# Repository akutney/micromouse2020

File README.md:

# Getting Started

Get started with the following links:

- [Environment Setup](docs/Environment%20Setup.md)
- [Project Structure](docs/Project%20Structure.md)
- [Development Lifecycle](docs/Development%20Lifecycle.md)

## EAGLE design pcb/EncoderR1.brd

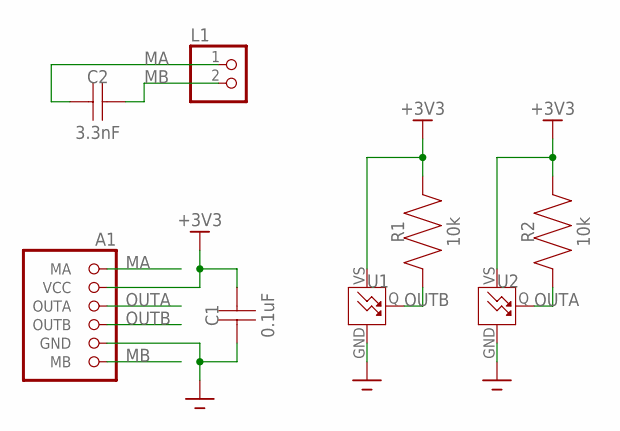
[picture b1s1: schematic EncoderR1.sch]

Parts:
A1: ENCODER; ENCODER-TAB
C1: 0.1uF; 0603
C2: 3.3nF; 0603
L1: MOTOR
R1, R2: 10k; 0603
U1, U2: TLE49462KHTSA1

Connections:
+3V3: A1.2 (VCC), C1.2, R1.2, R2.2, U1.VS, U2.VS
GND: A1.5 (GND), C1.1, U1.GND, U2.GND
MA: A1.1 (MA), C2.1, L1.1
MB: A1.6 (MB), C2.2, L1.2
OUTA: A1.3 (OUTA), R2.1, U2.Q
OUTB: A1.4 (OUTB), R1.1, U1.Q

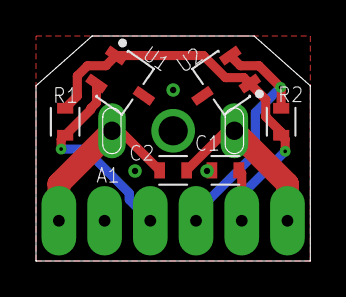
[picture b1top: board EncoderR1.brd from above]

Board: 2 copper layers, 15.2 x 12.5 mm, 8 parts (0 on the bottom side), 6 nets.

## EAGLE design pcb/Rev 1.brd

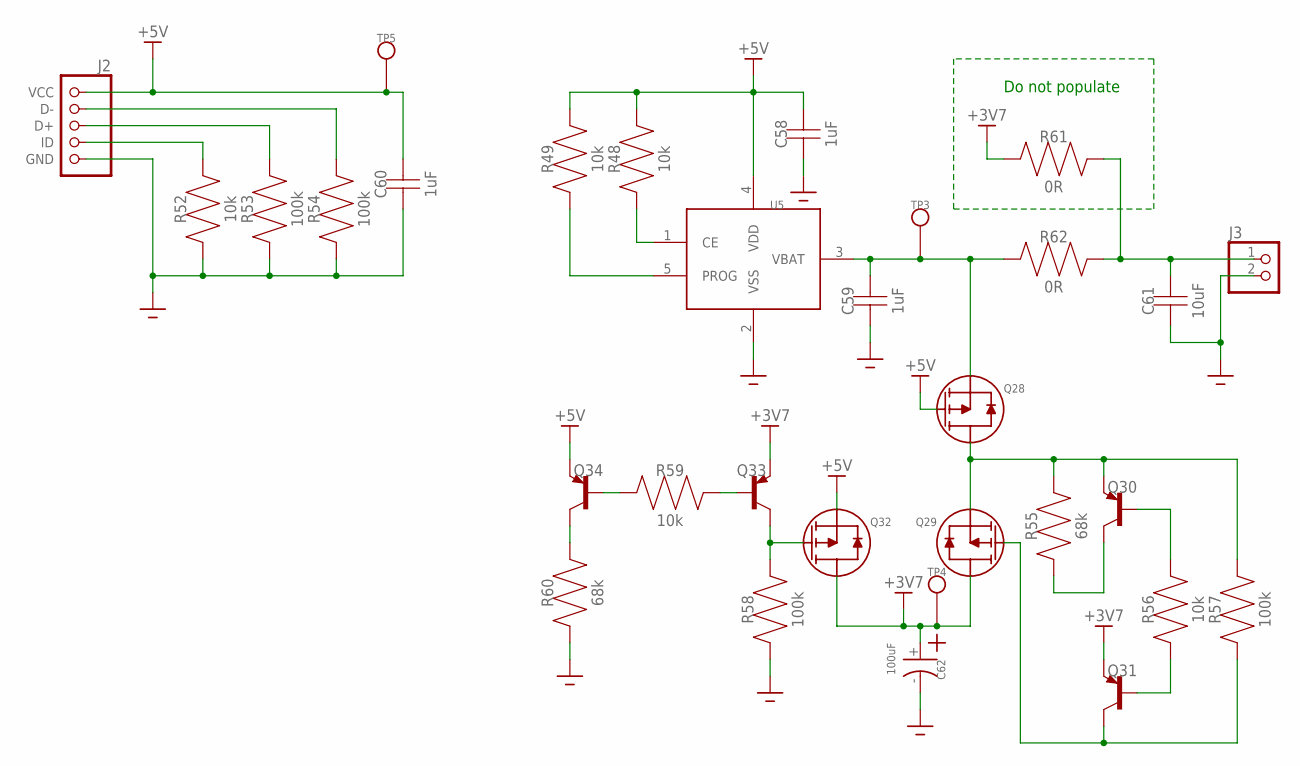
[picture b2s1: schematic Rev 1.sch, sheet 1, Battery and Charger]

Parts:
C58, C59, C60: 1uF; 0805
C61: 10uF; 0805
C62: 100uF; EEE-1EA101AP
J2: 10118194-0001LF
J3: B2B-PH-K-S(LF)(SN)
Q28, Q29, Q32: SI7157DP
Q30, Q31, Q33, Q34: MMBT3906; SOT96P237X112-3
R48, R49, R52: 10k; 0402
R53, R54: 100k; 0402
R55: 68k; 0603
R56: 10k; 0603
R57: 100k; 0603
R58: 100k; 0805
R59: 10k; 0805
R60: 68k; 0805
R61, R62: 0R; 0805
TP3, TP4, TP5: TESTPOINT
U5: MCP73811

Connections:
+3V7: C62.+, Q29.5 (D), Q29.6 (D), Q29.7 (D), Q29.8 (D), Q29.9 (D), Q29.10 (D), Q29.11 (D), Q31.2 (E), Q32.5 (D), Q32.6 (D), Q32.7 (D), Q32.8 (D), Q32.9 (D), Q32.10 (D), Q32.11 (D), Q33.2 (E), R61.P$1, TP4.P1; also elsewhere on the board
+5V: C58.P$2, C60.P$2, J2.1 (VCC), Q28.4 (G), Q32.1 (S), Q32.2 (S), Q32.3 (S), Q34.2 (E), R48.2, R49.2, TP5.P1, U5.4 (VDD)
GND: C58.P$1, C59.P$1, C60.P$1, C61.P$1, C62.-, J2.5 (GND), J2.6 (GND), J2.7 (GND), J2.8 (GND), J2.9 (GND), J2.10 (GND), J2.11 (GND), J2.12 (GND), J2.13 (GND), J2.14 (GND), J2.15 (GND), J3.2, R52.1, R53.1, R54.1, R58.P$1, R60.P$1, U5.2 (VSS); also elsewhere on the board
unnamed: C59.P$2, Q28.1 (S), Q28.2 (S), Q28.3 (S), R62.P$1, TP3.P1, U5.3 (VBAT)
unnamed: R48.1, U5.1 (CE)
unnamed: R49.1, U5.5 (PROG)
unnamed: Q30.3 (C), R55.1
unnamed: Q28.5 (D), Q28.6 (D), Q28.7 (D), Q28.8 (D), Q28.9 (D), Q28.10 (D), Q28.11 (D), Q29.1 (S), Q29.2 (S), Q29.3 (S), Q30.2 (E), R55.2, R57.2
unnamed: Q31.1 (B), R56.1
unnamed: Q30.1 (B), R56.2
unnamed: J2.4 (ID), R52.2
unnamed: J2.3 (D+), R53.2
unnamed: J2.2 (D-), R54.2
unnamed: Q29.4 (G), Q31.3 (C), R57.1
unnamed: Q32.4 (G), Q33.3 (C), R58.P$2
unnamed: Q34.1 (B), R59.P$1
unnamed: Q33.1 (B), R59.P$2
unnamed: Q34.3 (C), R60.P$2
unnamed: C61.P$2, J3.1, R61.P$2, R62.P$2

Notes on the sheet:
Do not populate

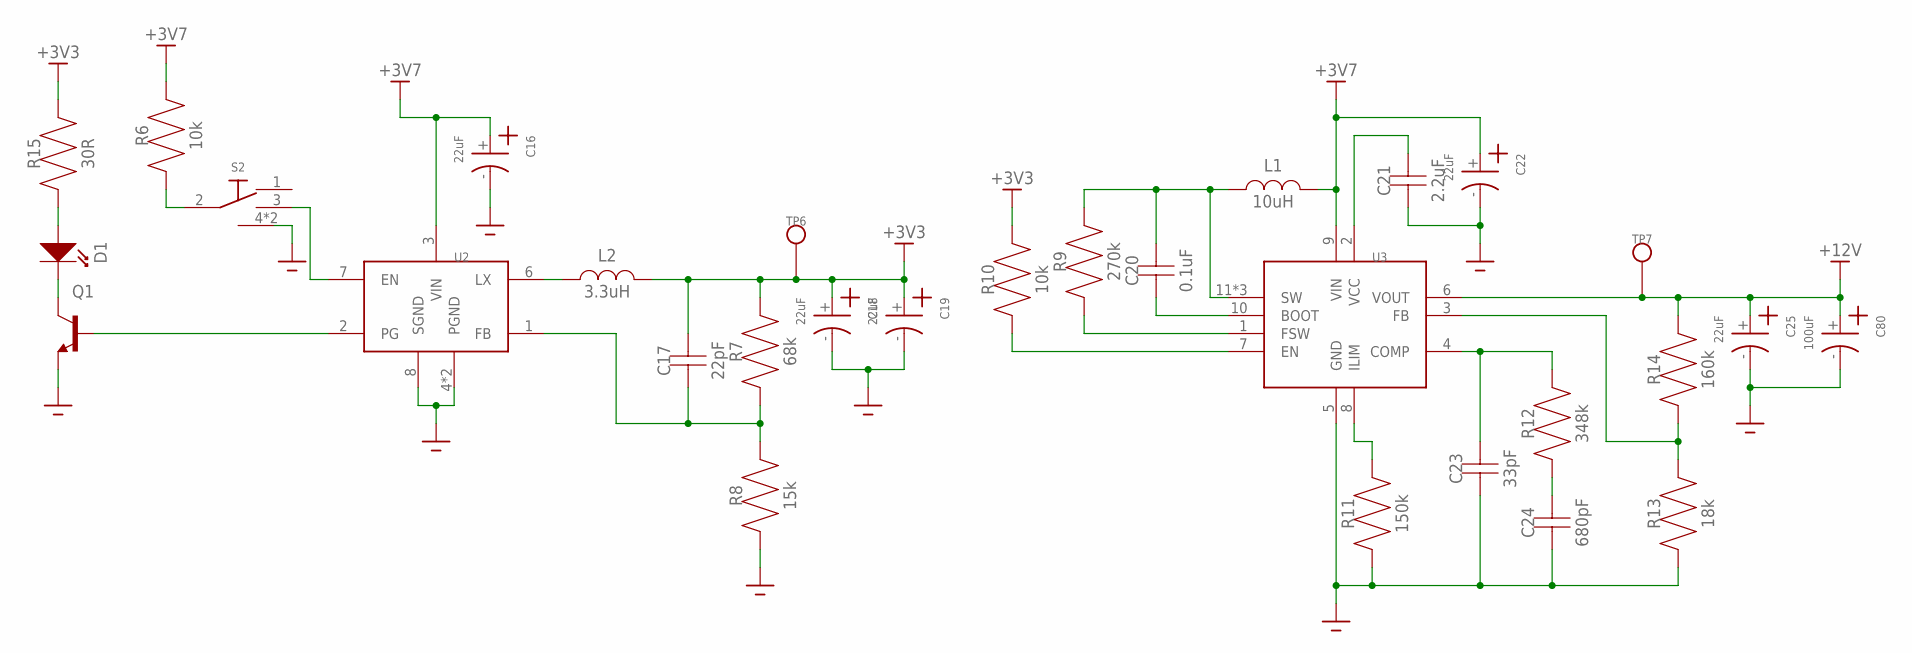
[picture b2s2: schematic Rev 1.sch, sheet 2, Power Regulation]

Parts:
C16, C18, C19, C22, C25: 22uF; 865080542006
C17: 22pF; 0805
C20: 0.1uF; 0402
C21: 2.2uF; 0402
C23: 33pF; 0402
C24: 680pF; 0402
C80: 100uF; EEE-1EA101AP
D1: LED1206; 1206
L1: 10uH; 104CDMCC
L2: 3.3uH; NRS5040
Q1: MMBT3904,215MMBT3904,215; SOT95P230X110-3
R6: 10k; 0805
R7: 68k; 0805
R8: 15k; 0805
R9: 270k; 0402
R10: 10k; 0603
R11: 150k; 0603
R12: 348k; 0402
R13: 18k; 0402
R14: 160k; 0402
R15: 30R; 0805
S2: OS102011MS2QN1
TP6, TP7: TESTPOINT
U2: AP3441
U3: TPS61089

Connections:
+3V3: C17.P$2, C18.+, C19.+, L2.2, R7.P$2, R10.2, R15.P$2, TP6.P1; also elsewhere on the board
+3V7: C16.+, C22.+, L1.2, R6.P$2, U2.3 (VIN), U3.9 (VIN); also elsewhere on the board
+12V: C25.+, C80.+, R14.2, TP7.P1, U3.6 (VOUT); also elsewhere on the board
GND: C16.-, C18.-, C19.-, C21.1, C22.-, C23.1, C24.1, C25.-, C80.-, Q1.2 (E), R8.P$1, R11.1, R13.1, S2.4 (GND), S2.5 (GND), U2.4 (PGND), U2.8 (SGND), U2.9 (PGND), U3.5 (GND); also elsewhere on the board
unnamed: L2.1, U2.6 (LX)
unnamed: C17.P$1, R7.P$1, R8.P$2, U2.1 (FB)
unnamed: S2.3 (2), U2.7 (EN)
unnamed: R6.P$1, S2.2 (COMMON)
unnamed: C20.1, U3.10 (BOOT)
unnamed: R9.1, U3.1 (FSW)
unnamed: C20.2, L1.1, R9.2, U3.11 (SW), U3.12 (SW), U3.13 (SW)
unnamed: R11.2, U3.8 (ILIM)
unnamed: C21.2, U3.2 (VCC)
unnamed: C23.2, R12.2, U3.4 (COMP)
unnamed: R10.1, U3.7 (EN)
unnamed: C24.2, R12.1
unnamed: Q1.1 (B), U2.2 (PG)
unnamed: R13.2, R14.1, U3.3 (FB)
unnamed: D1.2 (OUT), Q1.3 (C)
unnamed: D1.1 (IN), R15.P$1

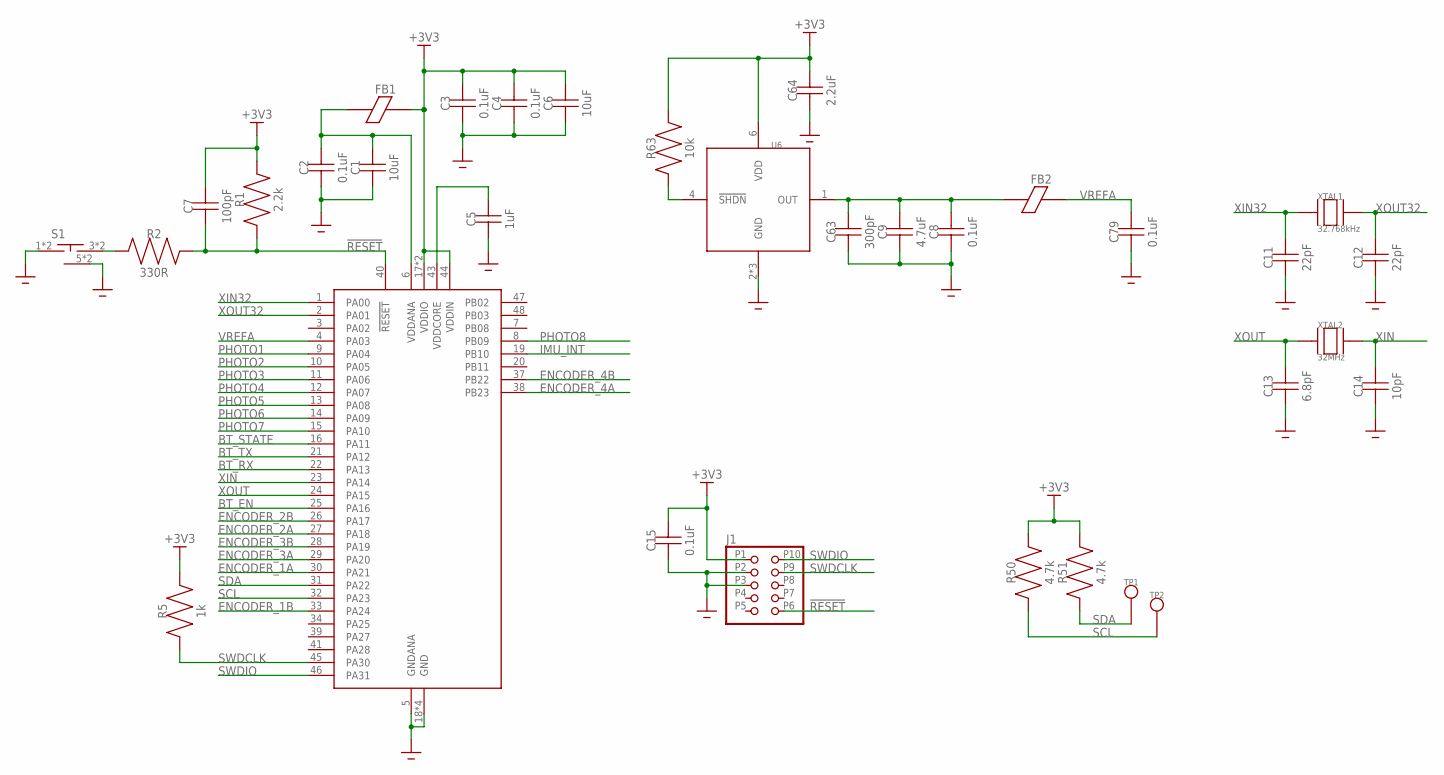
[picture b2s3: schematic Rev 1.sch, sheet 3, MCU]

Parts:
C1, C6: 10uF; 0402
C2, C3, C4, C8, C79: 0.1uF; 0402
C5: 1uF; 0402
C7: 100pF; 0603
C9: 4.7uF; 0402
C11, C12: 22pF; 0402
C13: 6.8pF; 0402
C14: 10pF; 0402
C15: 0.1uF; 0603
C63: 300pF; 0402
C64: 2.2uF; 0402
FB1, FB2: FERRITE0402; 0402
J1: 3220-10-0100-00
R1: 2.2k; 0603
R2: 330R; 0805
R5: 1k; 0603
R50, R51: 4.7k; 0603
R63: 10k; 0402
S1: PTS526SMG15SMTR2LFS
TP1, TP2: TESTPOINT
U1: ATSAMD21G18A-MU
U6: MCP1501
XTAL1: 32.768kHz; FC-135
XTAL2: 32MHz; XRCGB

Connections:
!RESET: C7.1, J1.P6 (6), R1.1, R2.P$2, U1.40 (!RESET)
+3V3: C3.2, C4.2, C6.2, C7.2, C15.2, C64.2, FB1.2, J1.P1 (1), R1.2, R5.2, R50.2, R51.2, R63.2, U1.17 (VDDIO), U1.36 (VDDIO), U1.44 (VDDIN), U6.6 (VDD); also elsewhere on the board
BT_EN: U1.25 (PA16); also elsewhere on the board
BT_RX: U1.22 (PA13); also elsewhere on the board
BT_STATE: U1.16 (PA11); also elsewhere on the board
BT_TX: U1.21 (PA12); also elsewhere on the board
ENCODER_1A: U1.30 (PA21); also elsewhere on the board
ENCODER_1B: U1.33 (PA24); also elsewhere on the board
ENCODER_2A: U1.27 (PA18); also elsewhere on the board
ENCODER_2B: U1.26 (PA17); also elsewhere on the board
ENCODER_3A: U1.29 (PA20); also elsewhere on the board
ENCODER_3B: U1.28 (PA19); also elsewhere on the board
ENCODER_4A: U1.38 (PB23); also elsewhere on the board
ENCODER_4B: U1.37 (PB22); also elsewhere on the board
GND: C1.1, C2.1, C3.1, C4.1, C5.1, C6.1, C8.1, C9.1, C11.1, C12.1, C13.1, C14.1, C15.1, C63.1, C64.1, C79.1, J1.P2 (2), J1.P3 (3), S1.1, S1.2 (1), S1.5 (GND), S1.6 (GND), U1.5 (GNDANA), U1.18 (GND), U1.35 (GND), U1.42 (GND), U1.49 (GND), U6.2 (GND), U6.3 (GND), U6.5 (GND); also elsewhere on the board
IMU_INT: U1.19 (PB10); also elsewhere on the board
unnamed: R2.P$1, S1.3 (2), S1.4 (2)
unnamed: C5.2, U1.43 (VDDCORE)
unnamed: C1.2, C2.2, FB1.1, U1.6 (VDDANA)
unnamed: R63.1, U6.4 (!SHDN)
unnamed: C8.2, C9.2, C63.2, FB2.1, U6.1 (OUT)
PHOTO1: U1.9 (PA04); also elsewhere on the board
PHOTO2: U1.10 (PA05); also elsewhere on the board
PHOTO3: U1.11 (PA06); also elsewhere on the board
PHOTO4: U1.12 (PA07); also elsewhere on the board
PHOTO5: U1.13 (PA08); also elsewhere on the board
PHOTO6: U1.14 (PA09); also elsewhere on the board
PHOTO7: U1.15 (PA10); also elsewhere on the board
PHOTO8: U1.8 (PB09); also elsewhere on the board
SCL: R50.1, TP2.P1, U1.32 (PA23); also elsewhere on the board
SDA: R51.1, TP1.P1, U1.31 (PA22); also elsewhere on the board
SWDCLK: J1.P9 (9), R5.1, U1.45 (PA30)
SWDIO: J1.P10 (10), U1.46 (PA31)
VREFA: C79.2, FB2.2, U1.4 (PA03)
XIN: C14.2, U1.23 (PA14), XTAL2.2, XTAL2.4
XIN32: C11.2, U1.1 (PA00), XTAL1.1
XOUT: C13.2, U1.24 (PA15), XTAL2.1, XTAL2.3
XOUT32: C12.2, U1.2 (PA01), XTAL1.2

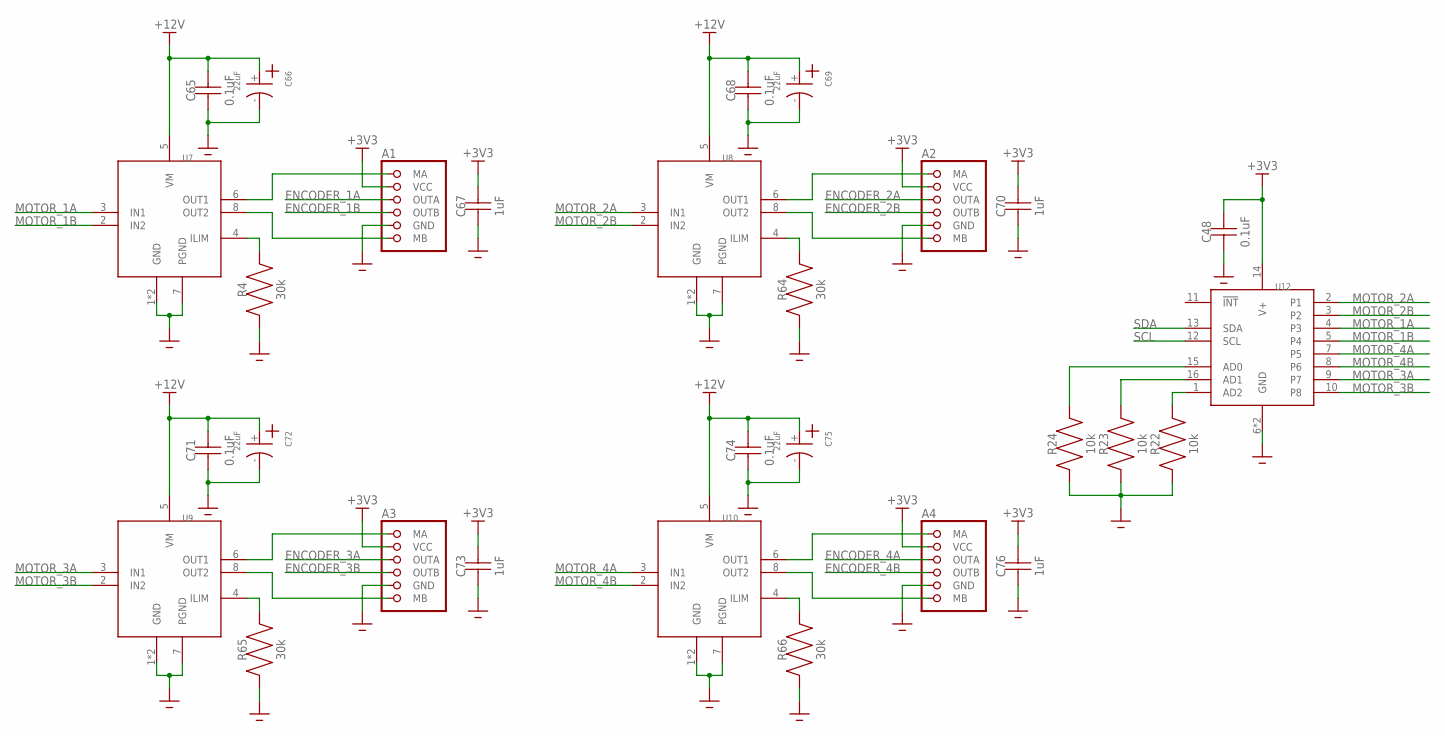
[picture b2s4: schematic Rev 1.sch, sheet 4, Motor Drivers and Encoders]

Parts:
A1, A2, A3, A4: ENCODERSLOT; ENCODER-SLOT
C48: 0.1uF; 0603
C65, C68, C71, C74: 0.1uF; 0805
C66, C69, C72, C75: 22uF; 865080542006
C67, C70, C73, C76: 1uF; 0805
R4, R64, R65, R66: 30k; 0805
R22, R23, R24: 10k; 0603
U7, U8, U9, U10: DRV8871
U12: MAX7315

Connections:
+3V3: A1.2 (VCC), A2.2 (VCC), A3.2 (VCC), A4.2 (VCC), C48.2, C67.P$2, C70.P$2, C73.P$2, C76.P$2, U12.14 (V+); also elsewhere on the board
+12V: C65.P$2, C66.+, C68.P$2, C69.+, C71.P$2, C72.+, C74.P$2, C75.+, U7.5 (VM), U8.5 (VM), U9.5 (VM), U10.5 (VM); also elsewhere on the board
ENCODER_1A: A1.3 (OUTA); also elsewhere on the board
ENCODER_1B: A1.4 (OUTB); also elsewhere on the board
ENCODER_2A: A2.3 (OUTA); also elsewhere on the board
ENCODER_2B: A2.4 (OUTB); also elsewhere on the board
ENCODER_3A: A3.3 (OUTA); also elsewhere on the board
ENCODER_3B: A3.4 (OUTB); also elsewhere on the board
ENCODER_4A: A4.3 (OUTA); also elsewhere on the board
ENCODER_4B: A4.4 (OUTB); also elsewhere on the board
GND: A1.5 (GND), A2.5 (GND), A3.5 (GND), A4.5 (GND), C48.1, C65.P$1, C66.-, C67.P$1, C68.P$1, C69.-, C70.P$1, C71.P$1, C72.-, C73.P$1, C74.P$1, C75.-, C76.P$1, R4.P$1, R22.1, R23.1, R24.1, R64.P$1, R65.P$1, R66.P$1, U7.1 (GND), U7.7 (PGND), U7.9 (GND), U8.1 (GND), U8.7 (PGND), U8.9 (GND), U9.1 (GND), U9.7 (PGND), U9.9 (GND), U10.1 (GND), U10.7 (PGND), U10.9 (GND), U12.6 (GND), U12.17 (GND); also elsewhere on the board
MOTOR_1A: U7.3 (IN1), U12.4 (P3)
MOTOR_1B: U7.2 (IN2), U12.5 (P4)
MOTOR_2A: U8.3 (IN1), U12.2 (P1)
MOTOR_2B: U8.2 (IN2), U12.3 (P2)
MOTOR_3A: U9.3 (IN1), U12.9 (P7)
MOTOR_3B: U9.2 (IN2), U12.10 (P8)
MOTOR_4A: U10.3 (IN1), U12.7 (P5)
MOTOR_4B: U10.2 (IN2), U12.8 (P6)
unnamed: R22.2, U12.1 (AD2)
unnamed: R23.2, U12.16 (AD1)
unnamed: R24.2, U12.15 (AD0)
unnamed: A1.1 (MA), U7.6 (OUT1)
unnamed: R4.P$2, U7.4 (ILIM)
unnamed: A1.6 (MB), U7.8 (OUT2)
unnamed: R64.P$2, U8.4 (ILIM)
unnamed: A2.1 (MA), U8.6 (OUT1)
unnamed: A2.6 (MB), U8.8 (OUT2)
unnamed: R65.P$2, U9.4 (ILIM)
unnamed: A3.1 (MA), U9.6 (OUT1)
unnamed: A3.6 (MB), U9.8 (OUT2)
unnamed: R66.P$2, U10.4 (ILIM)
unnamed: A4.1 (MA), U10.6 (OUT1)
unnamed: A4.6 (MB), U10.8 (OUT2)
SCL: U12.12 (SCL); also elsewhere on the board
SDA: U12.13 (SDA); also elsewhere on the board

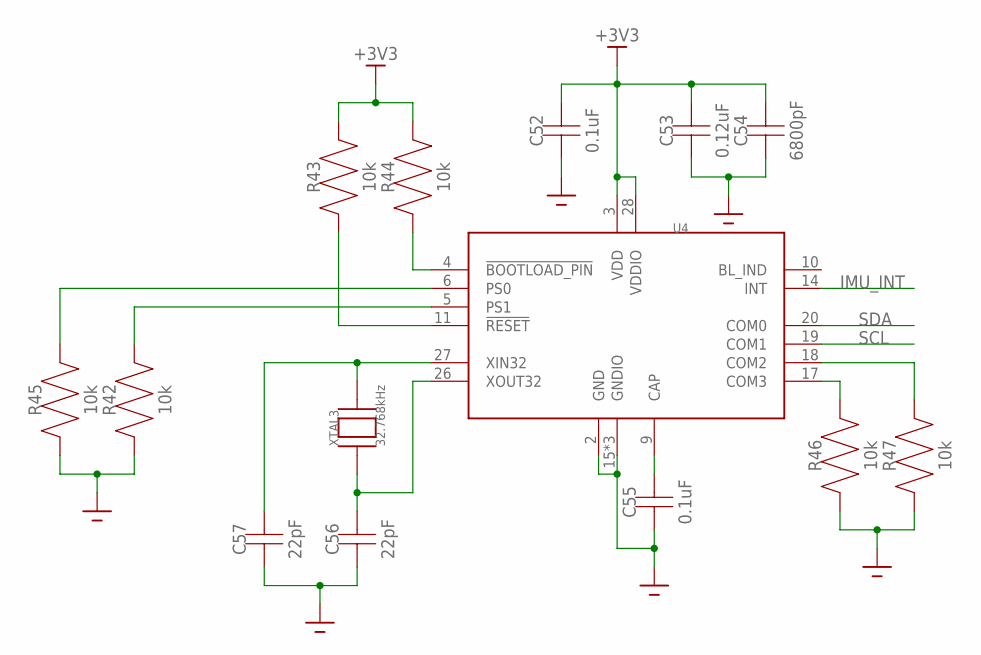
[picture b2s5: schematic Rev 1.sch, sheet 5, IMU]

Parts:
C52, C55: 0.1uF; 0603
C53: 0.12uF; 0603
C54: 6800pF; 0603
C56, C57: 22pF; 0603
R42, R43, R44, R45, R46, R47: 10k; 0603
U4: BNO055
XTAL3: 32.768kHz; FC-135

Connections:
+3V3: C52.2, C53.2, C54.2, R43.2, R44.2, U4.3 (VDD), U4.28 (VDDIO); also elsewhere on the board
GND: C52.1, C53.1, C54.1, C55.1, C56.1, C57.1, R42.1, R45.1, R46.1, R47.1, U4.2 (GND), U4.15 (GNDIO), U4.16 (GNDIO), U4.25 (GNDIO); also elsewhere on the board
IMU_INT: U4.14 (INT); also elsewhere on the board
unnamed: C55.2, U4.9 (CAP)
unnamed: R44.1, U4.4 (!BOOTLOAD_PIN)
unnamed: C56.2, U4.26 (XOUT32), XTAL3.1
unnamed: R42.2, U4.5 (PS1)
unnamed: C57.2, U4.27 (XIN32), XTAL3.2
unnamed: R45.2, U4.6 (PS0)
unnamed: R43.1, U4.11 (!RESET)
unnamed: R46.2, U4.17 (COM3)
unnamed: R47.2, U4.18 (COM2)
SCL: U4.19 (COM1); also elsewhere on the board
SDA: U4.20 (COM0); also elsewhere on the board

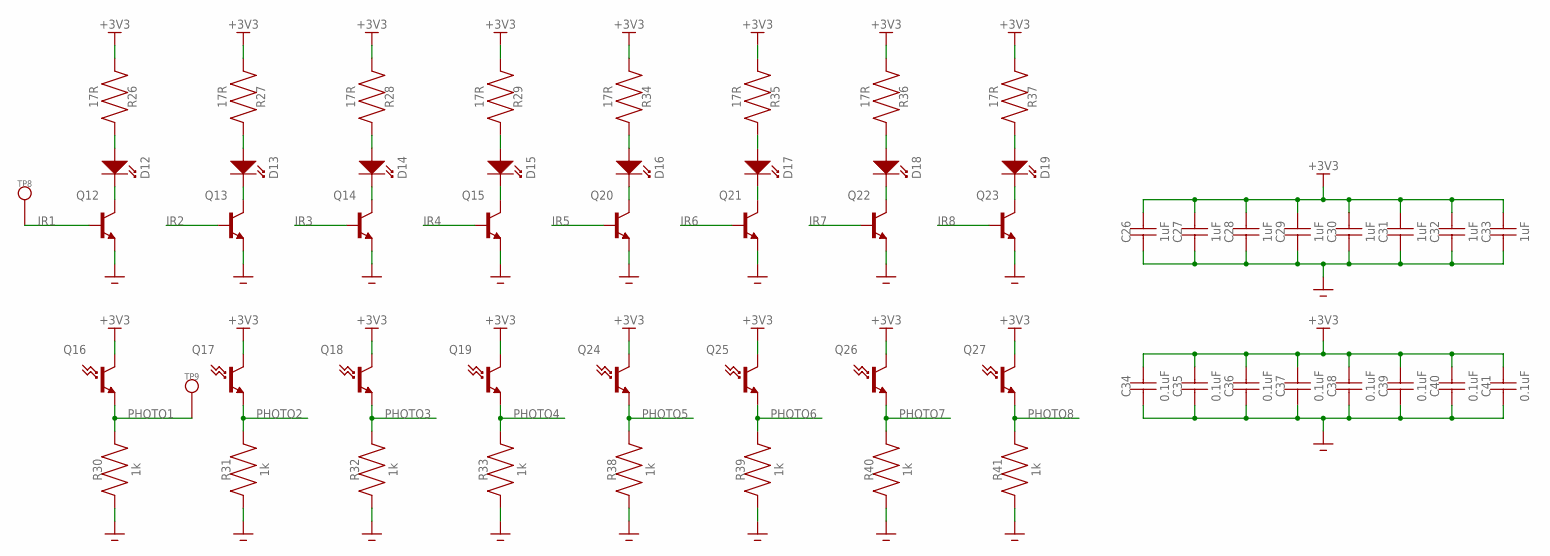
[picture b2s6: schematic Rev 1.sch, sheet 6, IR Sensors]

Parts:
C26, C27, C28, C29, C30, C31, C32: 1uF; 0805
C33: 1uF; 0603
C34, C35, C36, C37, C38, C39, C41: 0.1uF; 0805
C40: 0.1uF; 0603
D12, D13, D14, D15, D16, D17, D18, D19: SFH4545
Q12, Q13, Q14, Q15, Q20, Q21, Q22, Q23: MMBT3904,215MMBT3904,215; SOT95P230X110-3
Q16, Q17, Q18, Q19, Q24, Q25, Q26, Q27: TEFT4300
R26, R27, R28, R29, R34, R35, R36, R37: 17R; 0805
R30, R31, R32, R33, R38, R39, R41: 1k; 0805
R40: 1k; 0603
TP8, TP9: TESTPOINT

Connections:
+3V3: C26.P$2, C27.P$2, C28.P$2, C29.P$2, C30.P$2, C31.P$2, C32.P$2, C33.2, C34.P$2, C35.P$2, C36.P$2, C37.P$2, C38.P$2, C39.P$2, C40.2, C41.P$2, Q16.C, Q17.C, Q18.C, Q19.C, Q24.C, Q25.C, Q26.C, Q27.C, R26.P$1, R27.P$1, R28.P$1, R29.P$1, R34.P$1, R35.P$1, R36.P$1, R37.P$1; also elsewhere on the board
GND: C26.P$1, C27.P$1, C28.P$1, C29.P$1, C30.P$1, C31.P$1, C32.P$1, C33.1, C34.P$1, C35.P$1, C36.P$1, C37.P$1, C38.P$1, C39.P$1, C40.1, C41.P$1, Q12.2 (E), Q13.2 (E), Q14.2 (E), Q15.2 (E), Q20.2 (E), Q21.2 (E), Q22.2 (E), Q23.2 (E), R30.P$1, R31.P$1, R32.P$1, R33.P$1, R38.P$1, R39.P$1, R40.1, R41.P$1; also elsewhere on the board
IR1: Q12.1 (B), TP8.P1; also elsewhere on the board
IR2: Q13.1 (B); also elsewhere on the board
IR3: Q14.1 (B); also elsewhere on the board
IR4: Q15.1 (B); also elsewhere on the board
IR5: Q20.1 (B); also elsewhere on the board
IR6: Q21.1 (B); also elsewhere on the board
IR7: Q22.1 (B); also elsewhere on the board
IR8: Q23.1 (B); also elsewhere on the board
unnamed: D12.- (OUT), Q12.3 (C)
unnamed: D12.+ (IN), R26.P$2
unnamed: D13.- (OUT), Q13.3 (C)
unnamed: D13.+ (IN), R27.P$2
unnamed: D14.- (OUT), Q14.3 (C)
unnamed: D14.+ (IN), R28.P$2
unnamed: D15.- (OUT), Q15.3 (C)
unnamed: D15.+ (IN), R29.P$2
unnamed: D16.- (OUT), Q20.3 (C)
unnamed: D16.+ (IN), R34.P$2
unnamed: D17.- (OUT), Q21.3 (C)
unnamed: D17.+ (IN), R35.P$2
unnamed: D18.- (OUT), Q22.3 (C)
unnamed: D18.+ (IN), R36.P$2
unnamed: D19.- (OUT), Q23.3 (C)
unnamed: D19.+ (IN), R37.P$2
PHOTO1: Q16.E, R30.P$2, TP9.P1; also elsewhere on the board
PHOTO2: Q17.E, R31.P$2; also elsewhere on the board
PHOTO3: Q18.E, R32.P$2; also elsewhere on the board
PHOTO4: Q19.E, R33.P$2; also elsewhere on the board
PHOTO5: Q24.E, R38.P$2; also elsewhere on the board
PHOTO6: Q25.E, R39.P$2; also elsewhere on the board
PHOTO7: Q26.E, R40.2; also elsewhere on the board
PHOTO8: Q27.E, R41.P$2; also elsewhere on the board

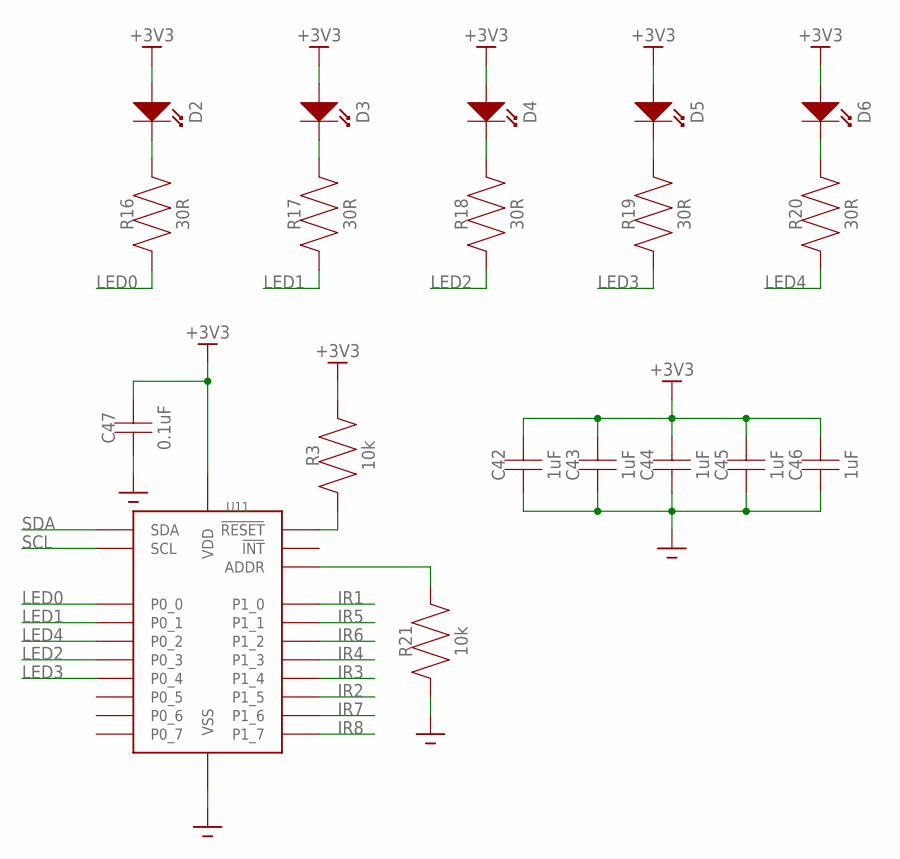
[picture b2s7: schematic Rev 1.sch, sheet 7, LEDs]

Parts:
C42, C43, C44, C45, C46: 1uF; 0603
C47: 0.1uF; 0603
D2, D3, D4, D5, D6: LED1206; 1206
R3, R21: 10k; 0603
R16, R17, R18, R19, R20: 30R; 0603
U11: PCAL6416A

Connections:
+3V3: C42.2, C43.2, C44.2, C45.2, C46.2, C47.2, D2.1 (IN), D3.1 (IN), D4.1 (IN), D5.1 (IN), D6.1 (IN), R3.2, U11.21 (VDD), U11.23 (VDD); also elsewhere on the board
GND: C42.1, C43.1, C44.1, C45.1, C46.1, C47.1, R21.1, U11.9 (VSS), U11.25 (VSS); also elsewhere on the board
IR1: U11.10 (P1_0); also elsewhere on the board
IR2: U11.15 (P1_5); also elsewhere on the board
IR3: U11.14 (P1_4); also elsewhere on the board
IR4: U11.13 (P1_3); also elsewhere on the board
IR5: U11.11 (P1_1); also elsewhere on the board
IR6: U11.12 (P1_2); also elsewhere on the board
IR7: U11.16 (P1_6); also elsewhere on the board
IR8: U11.17 (P1_7); also elsewhere on the board
LED0: R16.1, U11.1 (P0_0)
LED1: R17.1, U11.2 (P0_1)
LED2: R18.1, U11.4 (P0_3)
LED3: R19.1, U11.5 (P0_4)
LED4: R20.1, U11.3 (P0_2)
unnamed: D2.2 (OUT), R16.2
unnamed: D3.2 (OUT), R17.2
unnamed: D4.2 (OUT), R18.2
unnamed: D5.2 (OUT), R19.2
unnamed: D6.2 (OUT), R20.2
unnamed: R3.1, U11.24 (!RESET)
unnamed: R21.2, U11.18 (ADDR)
SCL: U11.19 (SCL); also elsewhere on the board
SDA: U11.20 (SDA); also elsewhere on the board

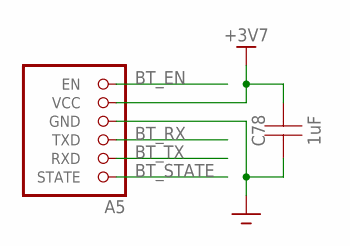
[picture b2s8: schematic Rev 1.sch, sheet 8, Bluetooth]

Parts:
A5: HC-05
C78: 1uF; 0603

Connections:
+3V7: A5.5 (VCC), C78.2; also elsewhere on the board
BT_EN: A5.6 (EN); also elsewhere on the board
BT_RX: A5.3 (TXD); also elsewhere on the board
BT_STATE: A5.1 (STATE); also elsewhere on the board
BT_TX: A5.2 (RXD); also elsewhere on the board
GND: A5.4 (GND), C78.1; also elsewhere on the board

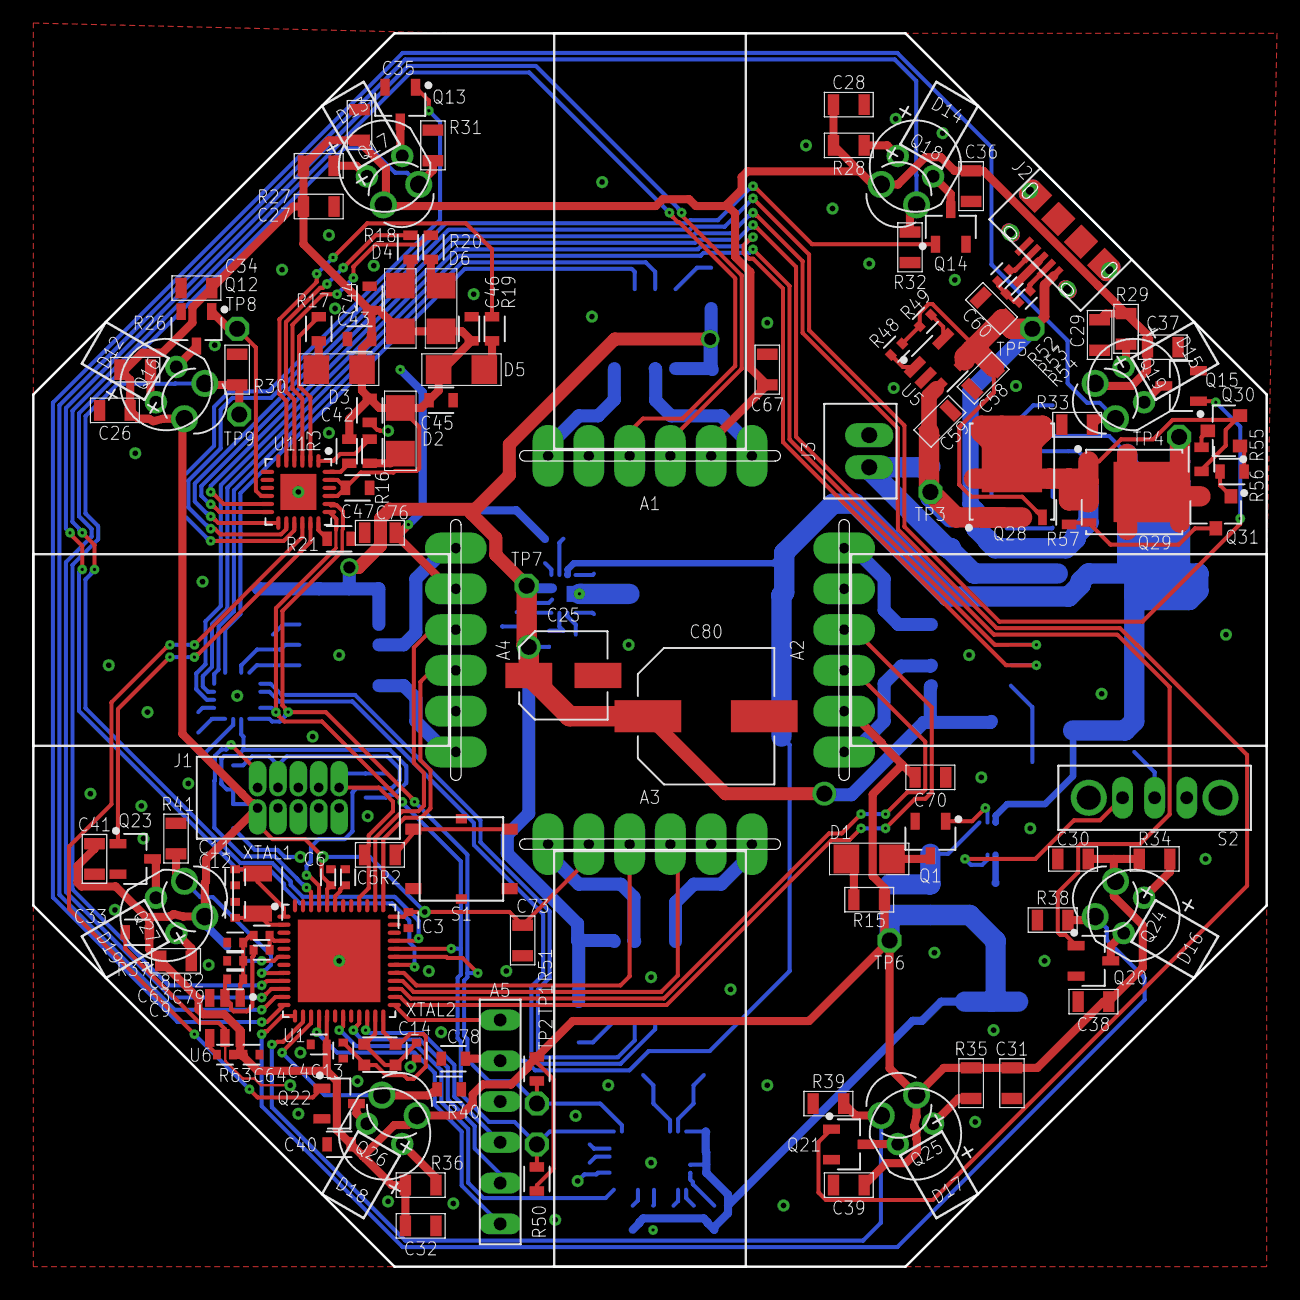
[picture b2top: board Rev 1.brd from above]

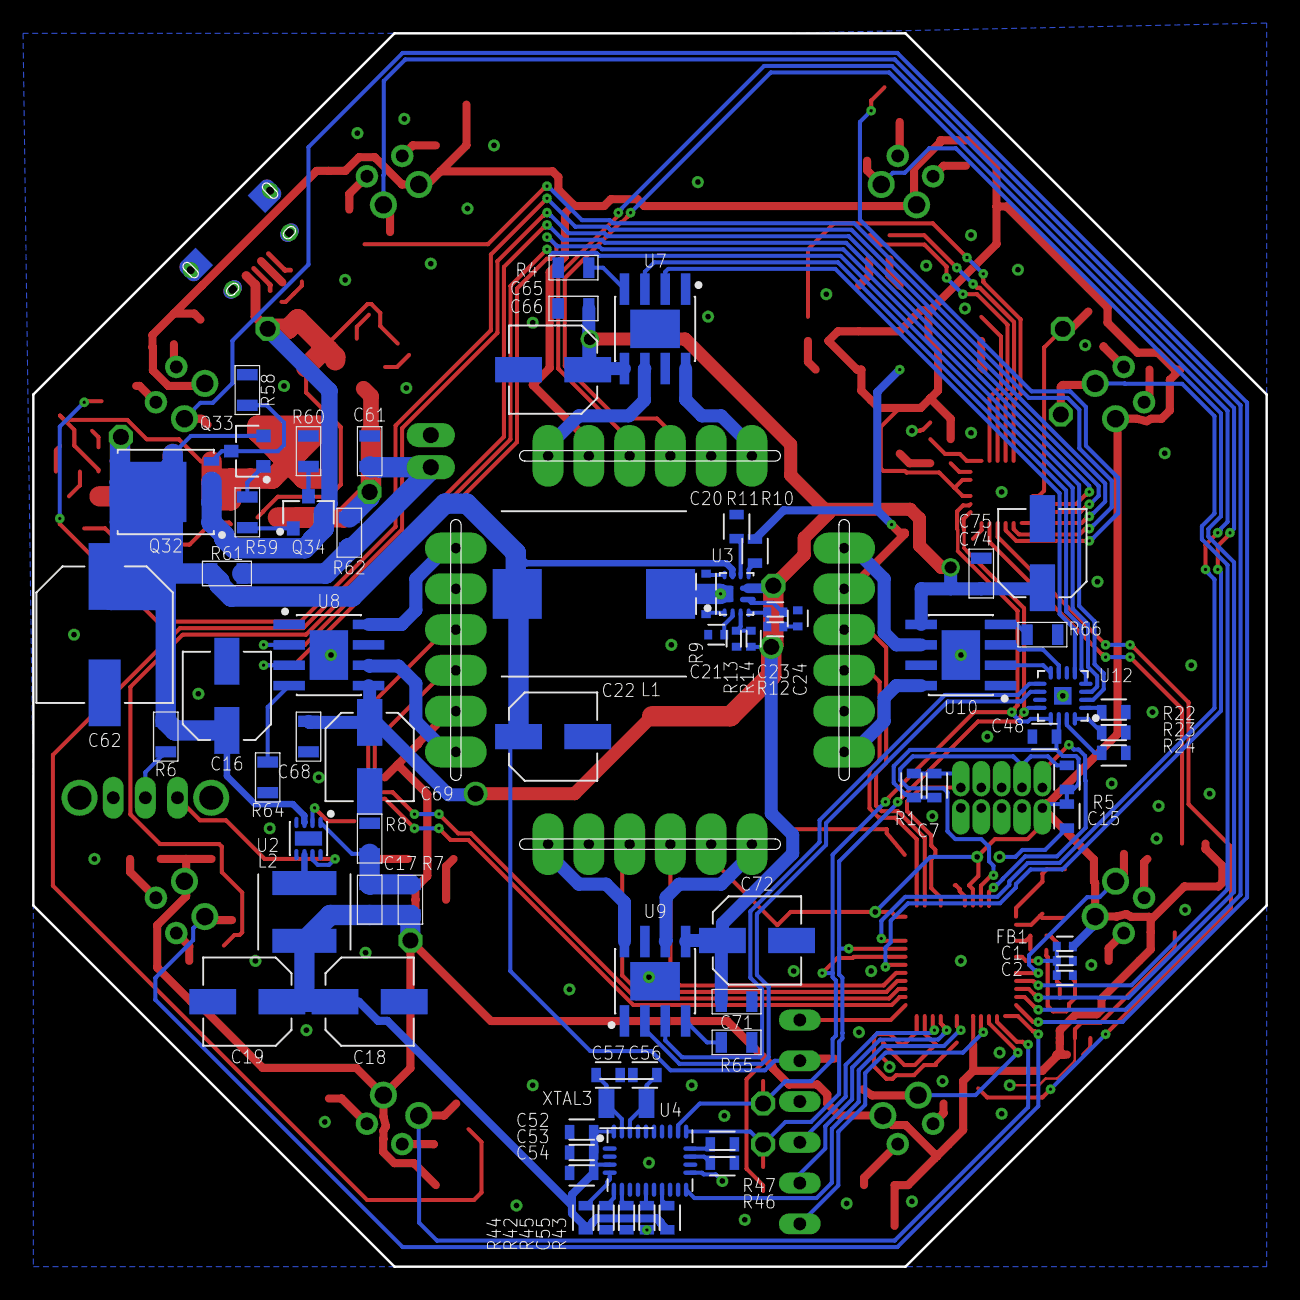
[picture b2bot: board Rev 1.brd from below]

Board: 2 copper layers, 76.8 x 76.8 mm, 216 parts (74 on the bottom side), 141 nets.

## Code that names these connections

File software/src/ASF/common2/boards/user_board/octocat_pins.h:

/*
 * octocat_pins.h
 */

#ifndef __OCTOCAT_PINS_H__
#define __OCTOCAT_PINS_H__

#include <stdint.h>
#include <types.h>


/* ----- Pin Definitions directly from schematic ----- */
// Clock Pins
extern pin_t XIN32;
extern pin_t XOUT32;
extern pin_t XIN;
extern pin_t XOUT;

// ADC Pins
extern pin_t VREFA;
extern pin_t PHOTO1;
extern pin_t PHOTO2;
extern pin_t PHOTO3;
extern pin_t PHOTO4;
extern pin_t PHOTO5;
extern pin_t PHOTO6;
extern pin_t PHOTO7;
extern pin_t PHOTO8;

// Bluetooth Serial Pins
extern pin_t BT_STATE;
extern pin_t BT_TX;
extern pin_t BT_RX;
extern pin_t BT_EN;

// Motor Encoders Pins
extern pin_t ENCODER_1A;
extern pin_t ENCODER_1B;
extern pin_t ENCODER_2A;
extern pin_t ENCODER_2B;
extern pin_t ENCODER_3A;
extern pin_t ENCODER_3B;
extern pin_t ENCODER_4A;
extern pin_t ENCODER_4B;

// IMU Pins
extern pin_t IMU_INT;

// I2C Pins
extern pin_t SDA;
extern pin_t SCL;

// Debugging Pins
extern pin_t SWDCLK;
extern pin_t SWDIO;

#endif /* __OCTOCAT_PINS_H__ */

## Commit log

2019-10-15 Created some parts
2019-10-17 Finished modeling the parts currently in the BOM
2019-10-17 Created .gitignore
2019-10-18 Added some more components to the library
2019-10-22 Started schematic layout
2019-10-25 Worked on the schematic some more
2019-11-12 Added starter Atmel Studio project
2019-11-12 Added comment to code
2019-11-12 add5 for kicks
2019-11-12 made a function to add 5
2019-11-13 fixed add5
2019-11-13 Moved .gitignore files around
2019-11-13 updated git ignore
2019-11-13 Actually removed the user file
2019-11-13 Started project setup, worked out configuration and driver interfaces
2019-11-20 Added GuidanceAlgorithm.h and dependencies for Dan
2019-11-20 Restructuring to set up testing framework
2019-11-20 Flipped north and south in probabalistic maze and standardized comment headers
2019-11-20 Added in Eigen Library and setup testing better
2019-11-20 Can almost build program with atmel studio
2019-11-20 Finished part library
2019-11-20 Did a lot of the schematic
2019-11-20 Added encoder schematic
2019-11-26 Updated the schematic
2019-12-04 Started to lay out board
2019-12-06 Put the components that have a specific location on the board
2019-12-06 Removed Eigen Library
2019-12-06 Implemented a GpioDriver with static functions
2019-12-10 Renamed General folder to Controller
2019-12-10 Setup clocks and SysTick
2019-12-10 Locked reference designators
2019-12-11 Sorted into groups
2019-12-11 Did some layout
2019-12-11 Started new c atmel asf project with stdio
2019-12-11 Fixed gitignore and added older clock
2019-12-11 fixed warning message
2019-12-11 Started on rtc counter driver
2019-12-11 Setup DFLL with conf_clocks.h
2019-12-11 Added channel selection to periperials
2019-12-11 slightly better commment
2019-12-11 moved geveric clock channel definitions to conf_board.h
2019-12-13 Added new ASF project
2019-12-13 Moved everything around
2019-12-13 Added first version of error framework
2019-12-13 Added drivers, types, and algorithms headers, disabled error framework
2019-12-14 Added documentation folder with helpful information
2019-12-14 Removed micromouse_main
2019-12-14 Changed documentation folder to docs
2019-12-14 Changed docs order
2019-12-14 Finished docs/
2019-12-14 Small fix in docs
2019-12-14 Set theme jekyll-theme-slate
2019-12-14 Added README.md to master
2019-12-15 Added code I forgot to commit earlier
2019-12-15 Fixed error.c compile errors
2019-12-27 Placed the majority of the components
2019-12-27 Placed the rest of the components
2019-12-27 Added note about pin mappings
2019-12-27 Removed the DIP switches and some LEDs
2020-01-02 Added IO expanders
2020-01-02 Placed and routed IO expanders
2020-01-02 Finished routing signals to MCU
2020-01-02 Created ground plane and fixed DRC
2020-01-02 Created encoder board
2020-01-02 Fixed passive type
2020-01-05 Created testing framework
2020-01-22 Added PDFs
2020-01-22 Fixed stupid Windows problems
2020-01-22 Fixed the stupid Windows problems the correct way
2020-01-22 Converted from old testing framework
2020-01-22 Removed test build files
2020-01-22 Removed some files and fixed others
2020-01-22 Removed other old files
2020-01-28 Made the docs slightly more pretty
2020-01-29 Fixed reference designators on silk screen
2020-01-30 Various Changes
2020-01-31 Added pin definitions from schmatic
2020-01-31 Used better PORT in Pin definitions
2020-01-31 Setup structure for timing
2020-01-31 Added init functions and setup main.c
2020-01-31 Implemented time_driver.c (untested)
2020-02-03 Generated part lists
2020-02-03 Fixed C7 that was somehow a resistor
2020-02-04 Fixed crystal package
2020-02-04 Switched power rail to HC-05
2020-02-04 Changed pin mapping
2020-02-07 Setup overall project architecture
2020-02-07 Fixed missing include
2020-02-07 Added missing comma
2020-02-11 Started setuping up drivers
2020-02-11 Drivers setup and builds with no warnings
2020-02-12 Setup individul test main()'s
2020-02-13 Implemented some adc funtionallity
2020-02-13 Added try_get_adc_data functionality to adc_driver
2020-02-13 added util/queue.c
2020-02-13 Successfull read multiple values
2020-02-14 Small Changes to adc_test
2020-02-18 finished tests on queue.tests.c and started converting guidance.c
2020-02-18 Fixed bluetooth on sparkfun board with special settings
2020-02-18 Started looking at distance_sensor_driver, but need to do i2c_driver first
2020-02-18 Started work on i2c config and driver
2020-02-18 Started implementing i2c_driver, changes critical section functions
2020-02-20 Added work to the guidance method
2020-02-20 Finished blocking wait implementation of i2c_driver.h
2020-02-20 Added imu i2c address
2020-02-21 Got more setup for the i2c things that use the i2c driver
2020-02-21 begun work on encoders in init.c
2020-02-21 Added #include "i2c_driver.h"
2020-02-25 defined encoder data
2020-02-25 work on the queue and guidance. current needs error fixing. but progress is progress
2020-02-25 Streamed data from adc over bluetooth
2020-02-25 Re-worked adc_driver to be callback based for use in distance_sensor_driver and start on distance_sensor_driver
2020-02-26 Wrote skeleton for matrix methods
2020-02-26 Created gerbers
2020-02-26 Added double-include protection
2020-02-26 Implemented the easy ones
2020-02-26 Implemented matrix multiplication
2020-02-26 Completed PCAL6416A
2020-02-27 Refactored and Completed distance_sensor_driver
2020-02-27 Setup imu_driver as disabled because it is not fully implemented
2020-02-28 commented out guidance. queue does not get errors, but test cases are not passing currently. need to fix that
2020-02-28 Setup pin configurations better and added support for sparkfun board
2020-02-28 Added linear regression tutorial
2020-03-05 completed model, started testing
2020-03-06 All queue methods but the swap one needing to be created works and is tested
2020-03-06 Changed LED driver to allow for LED to turn on and off when communicating with I/O expander
2020-03-15 Wrote foward and inverse omni models
2020-03-15 Create pi_motor_controller
2020-03-16 Did some simulations
2020-03-16 Made some pretty graphs
2020-03-16 Lots of error
2020-03-16 Changed to relative paths
2020-03-16 Updated sensor and motor definitions to new model
2020-03-16 Completed motor_driver and all dependencies
2020-03-28 Moved octave folder into software folder
